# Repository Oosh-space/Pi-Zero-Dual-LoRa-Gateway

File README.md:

# Pi Zero Dual LoRa Gateway
Dual LoRa Gateway HAT for the Pi Zero

# Introduction
Here is an attempt at creating a dual lora gateway for the Pi Zero as I wanted something small to track up to two trackers at once. Potentially from my pocket while I am running around a field looking for the trackers!! This board was intended to be used along with Dave Akermans LoRa Gateway software he developed for the Pi in The Sky project (https://github.com/PiInTheSky/lora-gateway.git) 

# Component Requirements 
* 1 x 20x2 pin header (female) 
* 1 x Hope RF LoRa Chip (the 2nd is optional) 
* 1 x SMA connector (the 2nd is optional) 
* 5 x 0805 SMD LEDs and appropriate resistors (optional) 

# Gerbers and boards 
For those of you familiar with board fabricators such as JLCPCB etc there is a gerber file for you to upload to get the board printed to make your own gateway. However boards are also available from my Ko-Fi page here: 

https://ko-fi.com/reganhimself/shop

# Setting up the Gateway
Once you have soldered up the board, you will need to install the LoRa Gateway software on your pi, Daves written a very easy to follow blog post about it here; 

https://www.daveakerman.com/?p=1719

# Support Me

If you found this board useful, why not buy me a coffee!

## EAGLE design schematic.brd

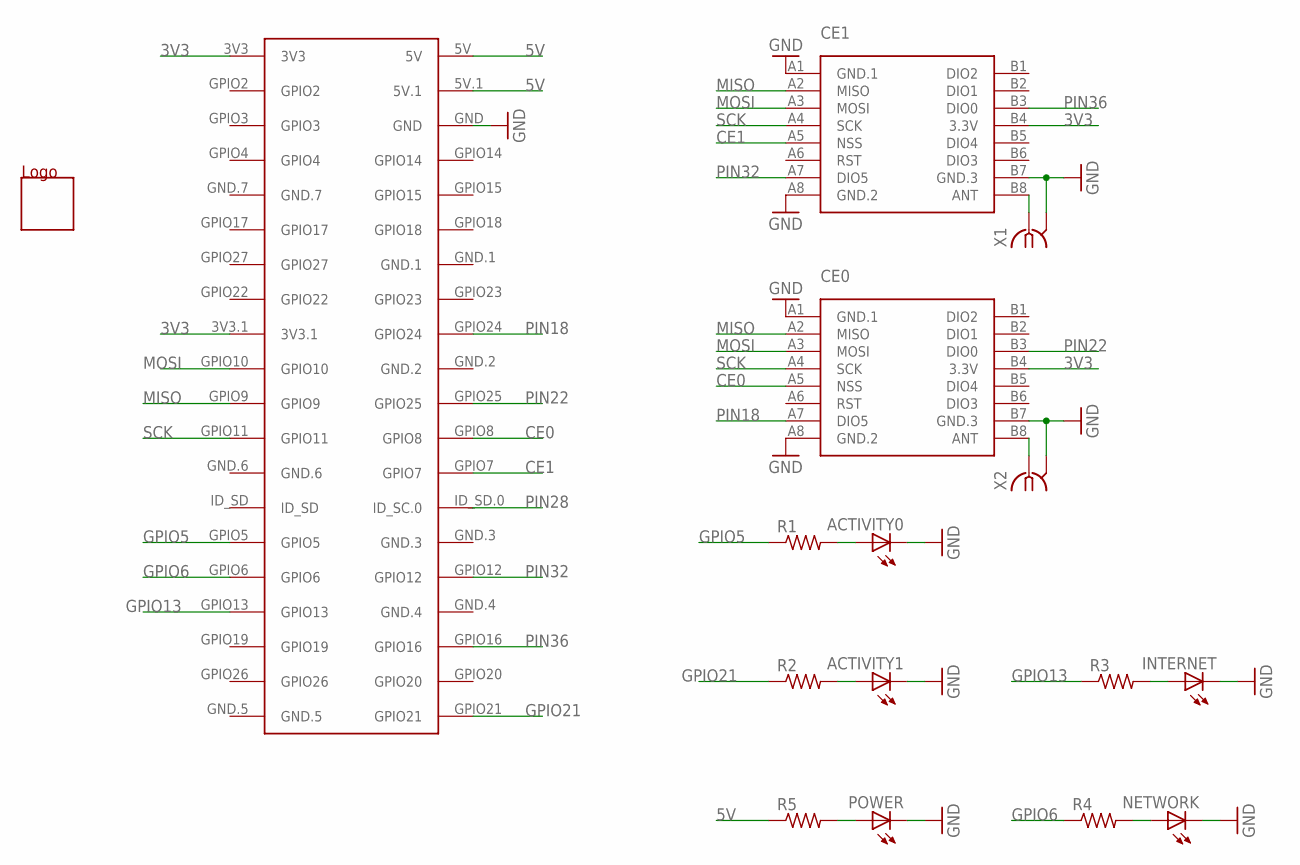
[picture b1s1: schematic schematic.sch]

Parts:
ACTIVITY0, ACTIVITY1: LEDCHIPLED_0805; CHIPLED_0805
CE0, CE1: WIRELESS-LORA-RFM95W#SMD
INTERNET: LEDCHIPLED_0805; CHIPLED_0805
NETWORK: LEDCHIPLED_0805; CHIPLED_0805
POWER: LEDCHIPLED_0805; CHIPLED_0805
R1, R2, R3, R4, R5: R-US_R0805; R0805
U$1: PIZERO
U$2: REGANLOGO
X1, X2: BU-SMA-V

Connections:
3V3: CE0.B4 (3.3V), CE1.B4 (3.3V), U$1.3V3, U$1.3V3.1
5V: R5.1, U$1.5V, U$1.5V.1
CE0: CE0.A5 (NSS), U$1.GPIO8
CE1: CE1.A5 (NSS), U$1.GPIO7
GND: ACTIVITY0.C, ACTIVITY1.C, CE0.A1 (GND.1), CE0.A8 (GND.2), CE0.B7 (GND.3), CE1.A1 (GND.1), CE1.A8 (GND.2), CE1.B7 (GND.3), INTERNET.C, NETWORK.C, POWER.C, U$1.GND, X1.2, X1.3 (2), X1.4 (2), X1.5 (2), X2.2, X2.3 (2), X2.4 (2), X2.5 (2)
GPIO5: R1.1, U$1.GPIO5
GPIO6: R4.1, U$1.GPIO6
GPIO13: R3.1, U$1.GPIO13
GPIO21: R2.1, U$1.GPIO21
MISO: CE0.A2 (MISO), CE1.A2 (MISO), U$1.GPIO9
MOSI: CE0.A3 (MOSI), CE1.A3 (MOSI), U$1.GPIO10
unnamed: ACTIVITY0.A, R1.2
unnamed: ACTIVITY1.A, R2.2
unnamed: INTERNET.A, R3.2
unnamed: NETWORK.A, R4.2
unnamed: POWER.A, R5.2
unnamed: CE1.B8 (ANT), X1.1
unnamed: CE0.B8 (ANT), X2.1
PIN18: CE0.A7 (DIO5), U$1.GPIO24
PIN22: CE0.B3 (DIO0), U$1.GPIO25
PIN28: U$1.ID_SD.0 (ID_SC.0)
PIN32: CE1.A7 (DIO5), U$1.GPIO12
PIN36: CE1.B3 (DIO0), U$1.GPIO16
SCK: CE0.A4 (SCK), CE1.A4 (SCK), U$1.GPIO11

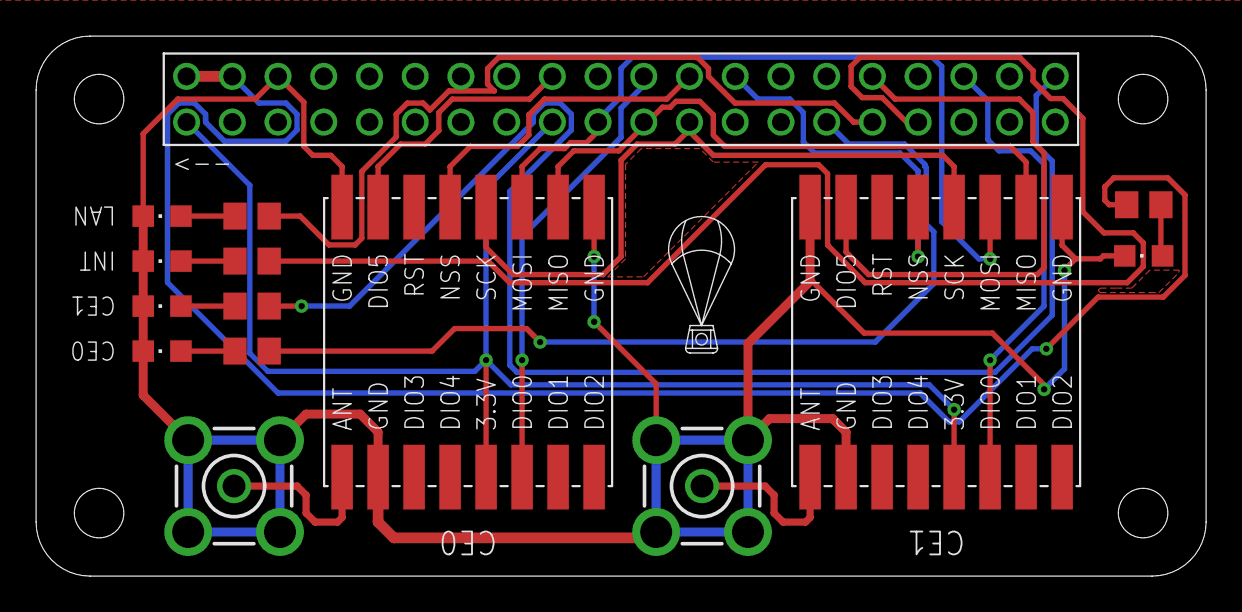
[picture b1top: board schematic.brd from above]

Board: 2 copper layers, 65.0 x 30.0 mm, 16 parts (0 on the bottom side), 23 nets.

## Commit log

2021-01-11 Add files via upload
    Initial file commit
2021-01-11 Update README.md
    updated details of readme

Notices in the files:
parts and their libraries:
diy-modules: Released under the Creative Commons Attribution 4.0 International License: http://creativecommons.org/licenses/by/4.0
